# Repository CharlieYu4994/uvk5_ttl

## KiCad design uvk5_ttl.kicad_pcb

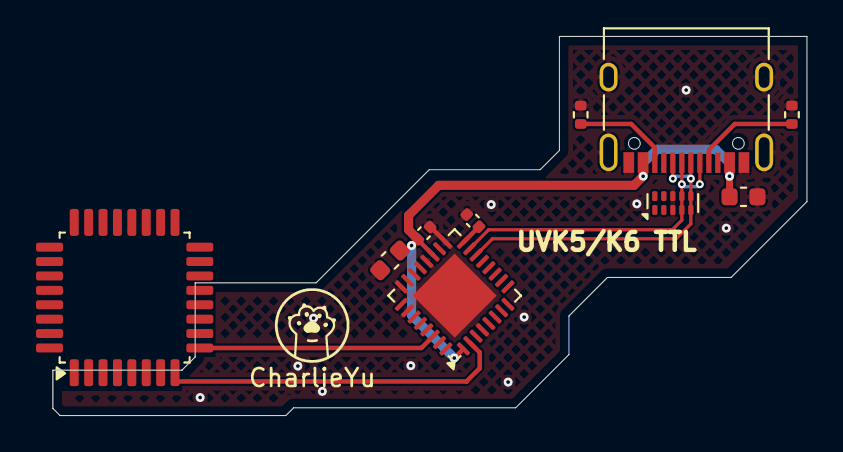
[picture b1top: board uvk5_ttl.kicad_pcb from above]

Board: 2 copper layers, 41.9 x 21.1 mm, 10 parts (0 on the bottom side), 7 nets.

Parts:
C1, C4: 100nF; C_0402_1005Metric
C2, C3: 4.7uF; C_0603_1608Metric
J1: USB_C_Receptacle_USB2.0; USB_C_Receptacle_XKB_U262-16XN-4BVC11
R1, R2: 5.1K; R_0402_1005Metric
RFF**: CharlieYu; charlieyu
U1: FT232RQ; QFN-32-1EP_5x5mm_P0.5mm_EP3.3x3.3mm
U2: TPD4E02B04DQA; USON-10_2.5x1.0mm_P0.5mm

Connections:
+5V: C1.1, C2.1, C3.1, J1.A4 (VBUS), J1.A9 (VBUS), J1.B4 (VBUS), J1.B9 (VBUS), U1.1 (VCCIO), U1.19 (VCC)
/D+: J1.A6 (D+), J1.B6 (D+), U1.14 (USBDP), U2.5 (IO4), U2.6 (NC)
/D-: J1.A7 (D-), J1.B7 (D-), U1.15 (USBDM), U2.4 (IO3), U2.7 (NC)
GND: C1.2, C2.2, C3.2, C4.2, J1.A1 (GND), J1.A12 (GND), J1.B1 (GND), J1.B12 (GND), J1.S1 (SHIELD), R1.2, R2.2, U1.4 (GND), U1.17 (GND), U1.20 (GND), U1.24 (AGND), U1.26 (TEST), U1.33 (EP), U2.3 (G), U2.8 (G)
unnamed: J1.A5 (CC1), R1.1
unnamed: J1.B5 (CC2), R2.1
unnamed: C4.1, U1.16 (3V3OUT)
